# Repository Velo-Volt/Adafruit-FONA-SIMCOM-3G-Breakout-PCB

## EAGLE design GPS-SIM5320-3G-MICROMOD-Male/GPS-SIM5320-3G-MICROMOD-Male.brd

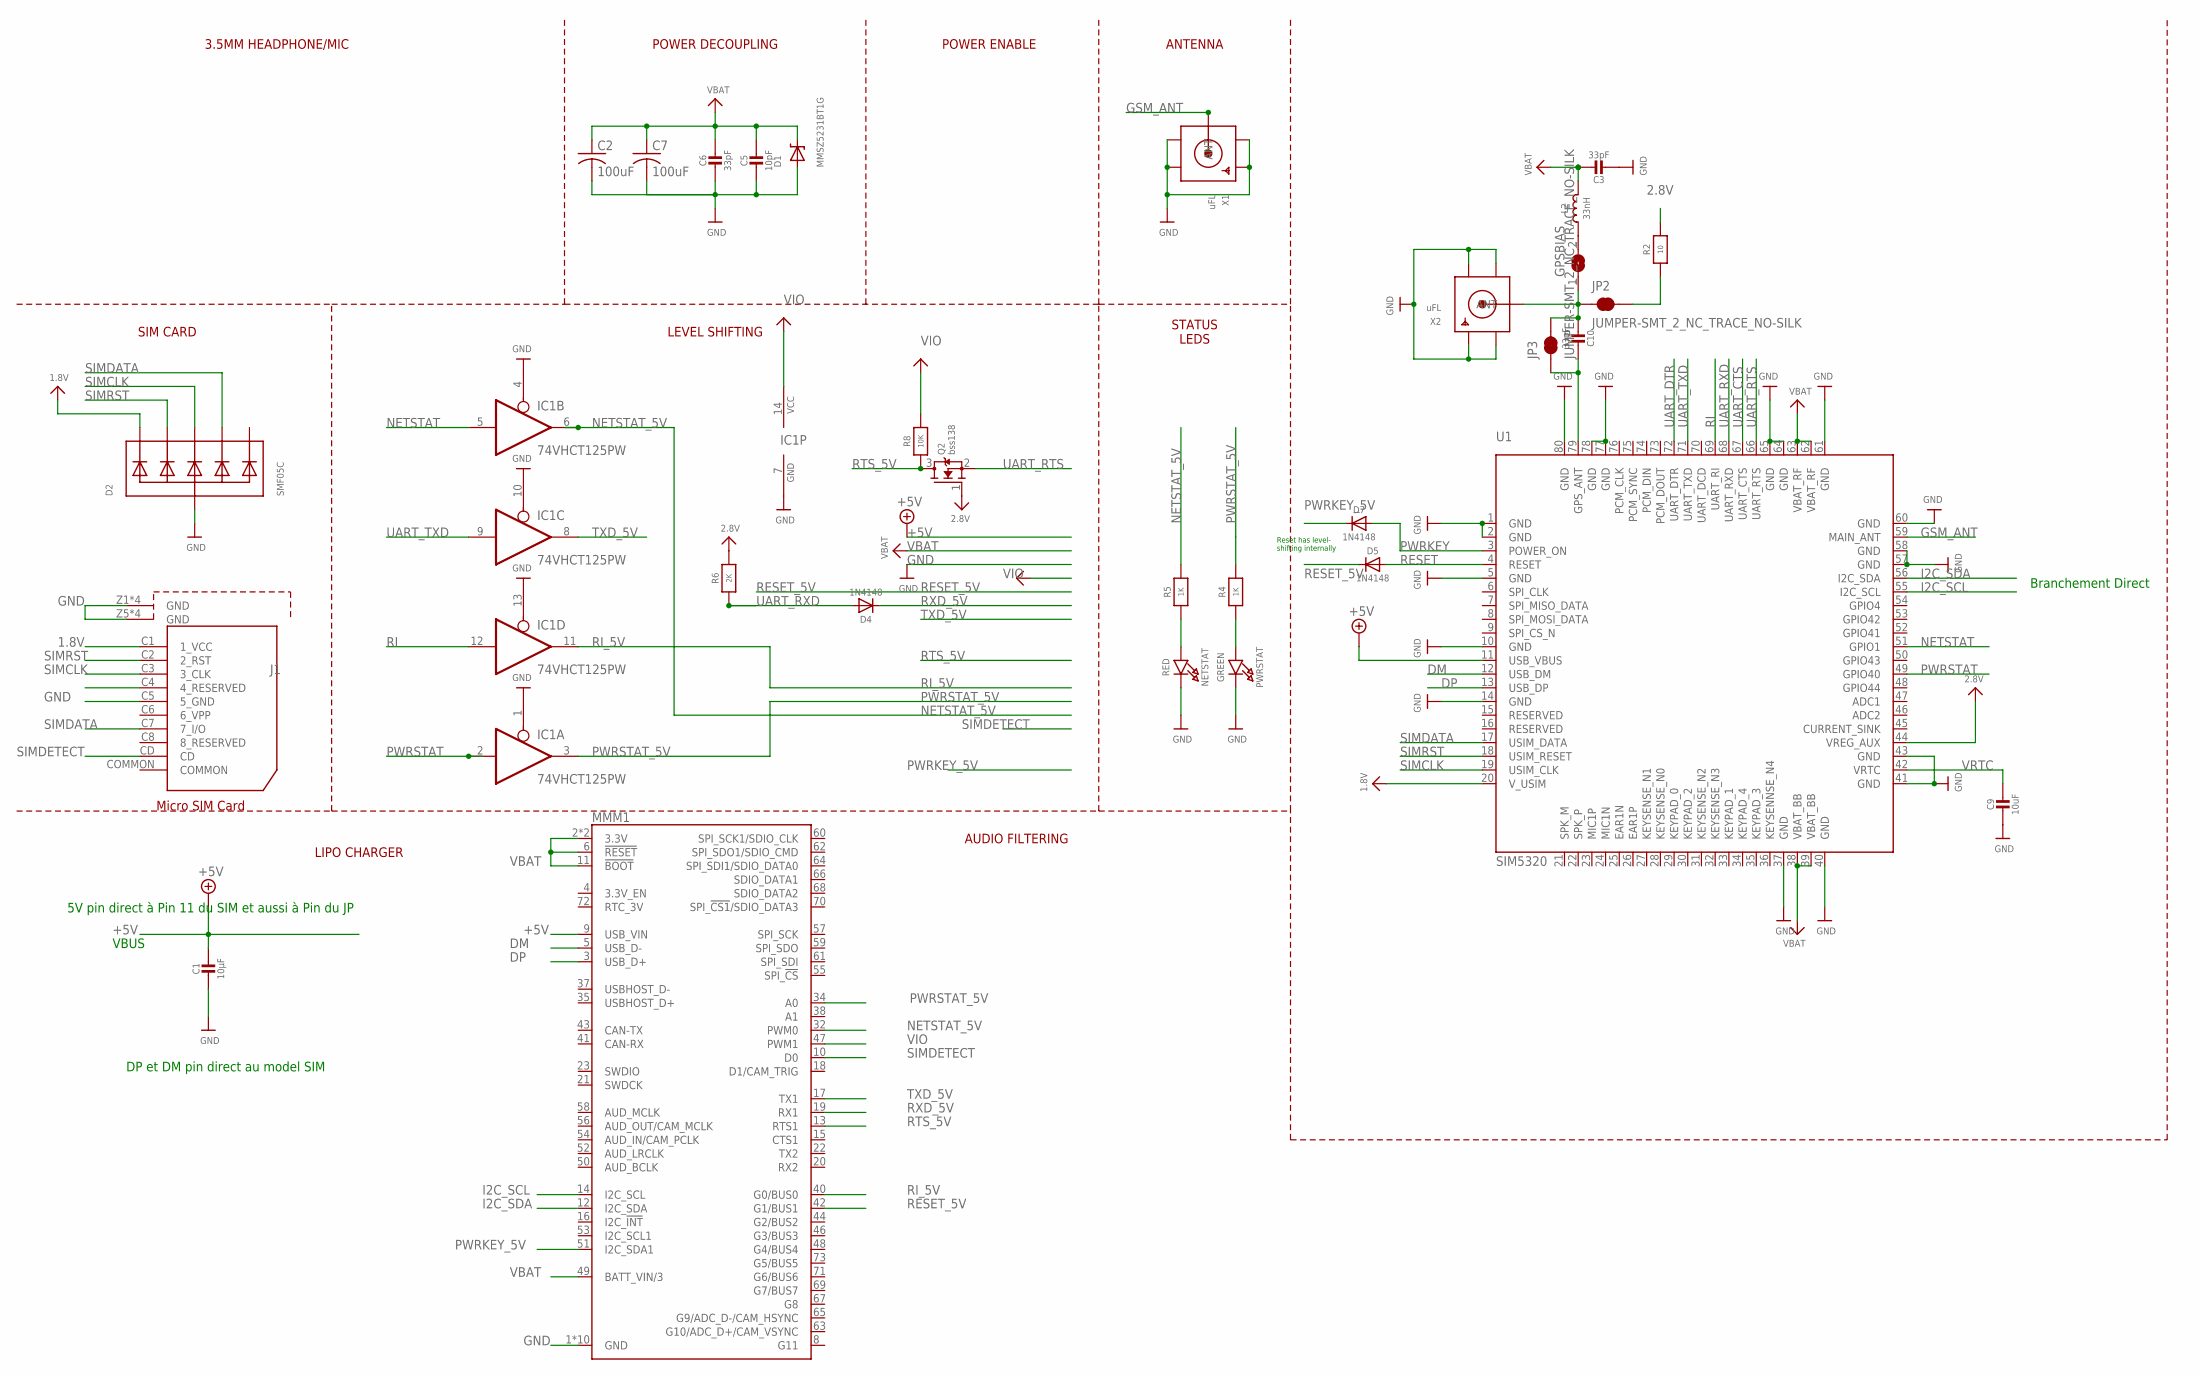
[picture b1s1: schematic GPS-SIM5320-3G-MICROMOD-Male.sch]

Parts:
C1: 10µF; 0805-NO
C2, C7: 100uF; C1210
C3, C6, C10: 33pF; 0805-NO
C5: 10pF; 0805-NO
C9: 10uF; 0805-NO
D1: MMSZ5231BT1G; SOD-123
D2: SMF05C; SOT363
D4, D5, D7: 1N4148; SOD-323
GPSBIAS: SOLDERJUMPER; SOLDERJUMPER_ARROW_NOPASTE
IC1: 74VHCT125PW; TSSOP14
J1: 693021010811
JP2, JP3: JUMPER-SMT_2_NC_TRACE_NO-SILK; SMT-JUMPER_2_NC_TRACE_NO-SILK
L2: 33nH; _0805MP
MMM1: MICROMOD_4222_MALE
NETSTAT: RED; CHIPLED_0805_NOOUTLINE
PWRSTAT: GREEN; CHIPLED_0805_NOOUTLINE
Q2: bss138; SOT23-WIDE
R2: 10; 0805-NO
R4, R5: 1K; 0805-NO
R6: 2K; 0805-NO
R8: 10K; 0805-NO
U1: SIM5320
X1, X2: uFL; SMA_EDGELAUNCH_UFL

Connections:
1.8V: D2.1 (C1), J1.C1 (1_VCC), U1.20 (V_USIM)
2.8V: Q2.1 (G), R2.2, R6.2, U1.44 (VREG_AUX)
+5V: C1.1, MMM1.9 (USB_VIN), U1.11 (USB_VBUS)
DM: MMM1.5 (USB_D-), U1.12 (USB_DM)
DP: MMM1.3 (USB_D+), U1.13 (USB_DP)
GND: C1.2, C2.2, C3.2, C5.2, C6.2, C7.2, C9.2, D1.A, D2.2 (A), IC1.1 (OE), IC1.4 (OE), IC1.7 (GND), IC1.10 (OE), IC1.13 (OE), J1.C5 (5_GND), J1.Z1 (GND), J1.Z2 (GND), J1.Z3 (GND), J1.Z4 (GND), J1.Z5 (GND), J1.Z6 (GND), J1.Z7 (GND), J1.Z8 (GND), MMM1.1 (GND), MMM1.7 (GND), MMM1.33 (GND), MMM1.36 (GND), MMM1.39 (GND), MMM1.45 (GND), MMM1.75 (GND), MMM1.GND1 (GND), MMM1.GND2 (GND), MMM1.GND3 (GND), NETSTAT.C, PWRSTAT.C, U1.1 (GND), U1.2 (GND), U1.5 (GND), U1.10 (GND), U1.14 (GND), U1.37 (GND), U1.40 (GND), U1.41 (GND), U1.43 (GND), U1.57 (GND), U1.58 (GND), U1.60 (GND), U1.61 (GND), U1.64 (GND), U1.65 (GND), U1.77 (GND), U1.78 (GND), U1.80 (GND), X1.GND@1 (GND1), X1.GND@2 (GND2), X1.GND@3 (GND3), X1.GND@4 (GND4), X2.GND@1 (GND1), X2.GND@2 (GND2), X2.GND@3 (GND3), X2.GND@4 (GND4)
GSM_ANT: U1.59 (MAIN_ANT), X1.P (ANT)
I2C_SCL: MMM1.14 (I2C_SCL), U1.55 (I2C_SCL)
I2C_SDA: MMM1.12 (I2C_SDA), U1.56 (I2C_SDA)
unnamed: C10.2, GPSBIAS.1, JP2.1, JP3.2, X2.P (ANT)
unnamed: C10.1, JP3.1, U1.79 (GPS_ANT)
unnamed: JP2.2, R2.1
unnamed: PWRSTAT.A, R4.1
unnamed: NETSTAT.A, R5.1
unnamed: GPSBIAS.2, L2.1
NETSTAT: IC1.5 (I), U1.51 (GPIO1)
NETSTAT_5V: IC1.6 (O), MMM1.32 (PWM0), R5.2
PWRKEY: D7.A, U1.3 (POWER_ON)
PWRKEY_5V: D7.C, MMM1.51 (I2C_SDA1)
PWRSTAT: IC1.2 (I), U1.49 (GPIO40)
PWRSTAT_5V: IC1.3 (O), MMM1.34 (A0), R4.2
RESET: D5.A, U1.4 (RESET)
RESET_5V: D5.C, MMM1.42 (G1/BUS1)
RI: IC1.12 (I), U1.69 (UART_RI)
RI_5V: IC1.11 (O), MMM1.40 (G0/BUS0)
RTS_5V: MMM1.13 (RTS1), Q2.3 (D), R8.1
RXD_5V: D4.C, MMM1.19 (RX1)
SIMCLK: D2.4 (C3), J1.C3 (3_CLK), U1.19 (USIM_CLK)
SIMDATA: D2.5 (C4), J1.C7 (7_I/O), U1.17 (USIM_DATA)
SIMDETECT: J1.CD, MMM1.10 (D0)
SIMRST: D2.3 (C2), J1.C2 (2_RST), U1.18 (USIM_RESET)
TXD_5V: IC1.8 (O), MMM1.17 (TX1)
UART_CTS: U1.67 (UART_CTS)
UART_DTR: U1.72 (UART_DTR)
UART_RTS: Q2.2 (S), U1.66 (UART_RTS)
UART_RXD: D4.A, R6.1, U1.68 (UART_RXD)
UART_TXD: IC1.9 (I), U1.71 (UART_TXD)
VBAT: C2.1, C3.1, C5.1, C6.1, C7.1, D1.C, L2.2, MMM1.2 (3.3V), MMM1.6 (!RESET!), MMM1.11 (!BOOT!), MMM1.49 (BATT_VIN/3), MMM1.74 (3.3V), U1.38 (VBAT_BB), U1.39 (VBAT_BB), U1.62 (VBAT_RF), U1.63 (VBAT_RF)
VIO: IC1.14 (VCC), MMM1.47 (PWM1), R8.2
VRTC: C9.1, U1.42 (VRTC)

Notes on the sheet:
ANTENNA
POWER DECOUPLING
3.5MM HEADPHONE/MIC
SIM CARD
LEVEL SHIFTING
LIPO CHARGER
AUDIO FILTERING
STATUS LEDS
POWER ENABLE
Reset has level- shifting internally
Branchement Direct
5V pin direct à Pin 11 du SIM et aussi à Pin du JP
DP et DM pin direct au model SIM
VBUS

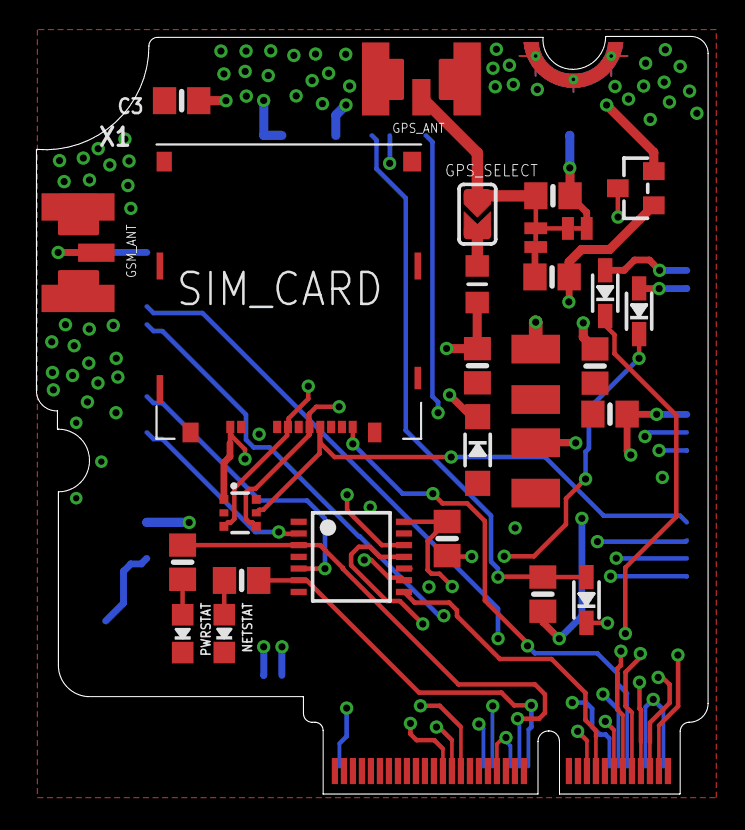
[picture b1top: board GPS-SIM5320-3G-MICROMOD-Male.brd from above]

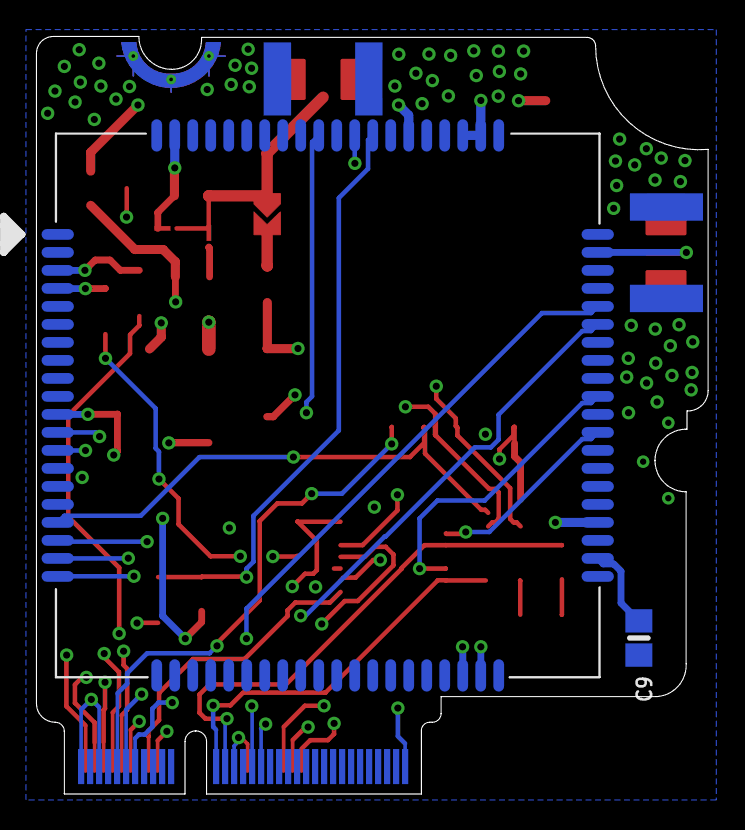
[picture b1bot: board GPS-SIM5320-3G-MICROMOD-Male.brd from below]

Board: 4 copper layers, 37.3 x 42.1 mm, 31 parts (2 on the bottom side), 38 nets.

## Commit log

2021-02-04 Create File

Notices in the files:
parts and their libraries:
microbuilder: This work is placed in the public domain, and may be freely used for commercial and non-commercial work with the following conditions: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
Wurth_Elektronik_Electromechanic_Input-O: Copyright: Würth Elektronik
